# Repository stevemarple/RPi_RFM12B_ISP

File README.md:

# RPi_RFM12B_ISP

RFM12B and Atmel ISP programmer shield for Raspberry Pi

## Avrdude

Use the patched version of avrdude from http://project-downloads.drogon.net/files/. I suggest copying the
.avrduderc file from the avrdude directory in this repository to your home directory. It will create create 
the correct definitions for two new programmers, gpio0 for the onboard microcontroller and gpio1 for programming
other microcontrollers.

## Using the Arduino IDE

If you do not have a <code>hardware</code> directory inside your Arduino <code>sketchbook</code> folder
then create one. Copy the raspi directory and its entire contents to the hardware directory. Restart the 
Arduino IDE. You should now have two new board options, <code>ATmega328 @ 8MHz on RasPi</code> and 
<code>ATmega328P @ 8MHz on RasPi</code>. Select the one which matches the microcontroller. There are also two new
programmers; <code>Raspberry Pi GPIO (onboard)</code> and <code>Raspberry Pi GPIO (external ISP)</code>. 
The onboard one will be used automatically to upload new sketches to the RFM12B/ISP shield. The external ISP
programmer can be selected to program other microcontrollers from within the Arduino IDE.

## License

Unless indicated otherwise hardware is released under the Creative
Commons Attribution-ShareAlike 3.0 Unported (CC BY-SA 3.0)
http://creativecommons.org/licenses/by-sa/3.0/

Unless indicated otherwise software is released under the GNU Lesser
General Public License, version 2.1.
http://www.gnu.org/licenses/lgpl-2.1.html

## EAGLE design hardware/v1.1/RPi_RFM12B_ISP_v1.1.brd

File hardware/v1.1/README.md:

# RPi_RFM12B_ISP v1.1

Adds the reset line which was missing for the external programmer on
v1.

**Not tested**

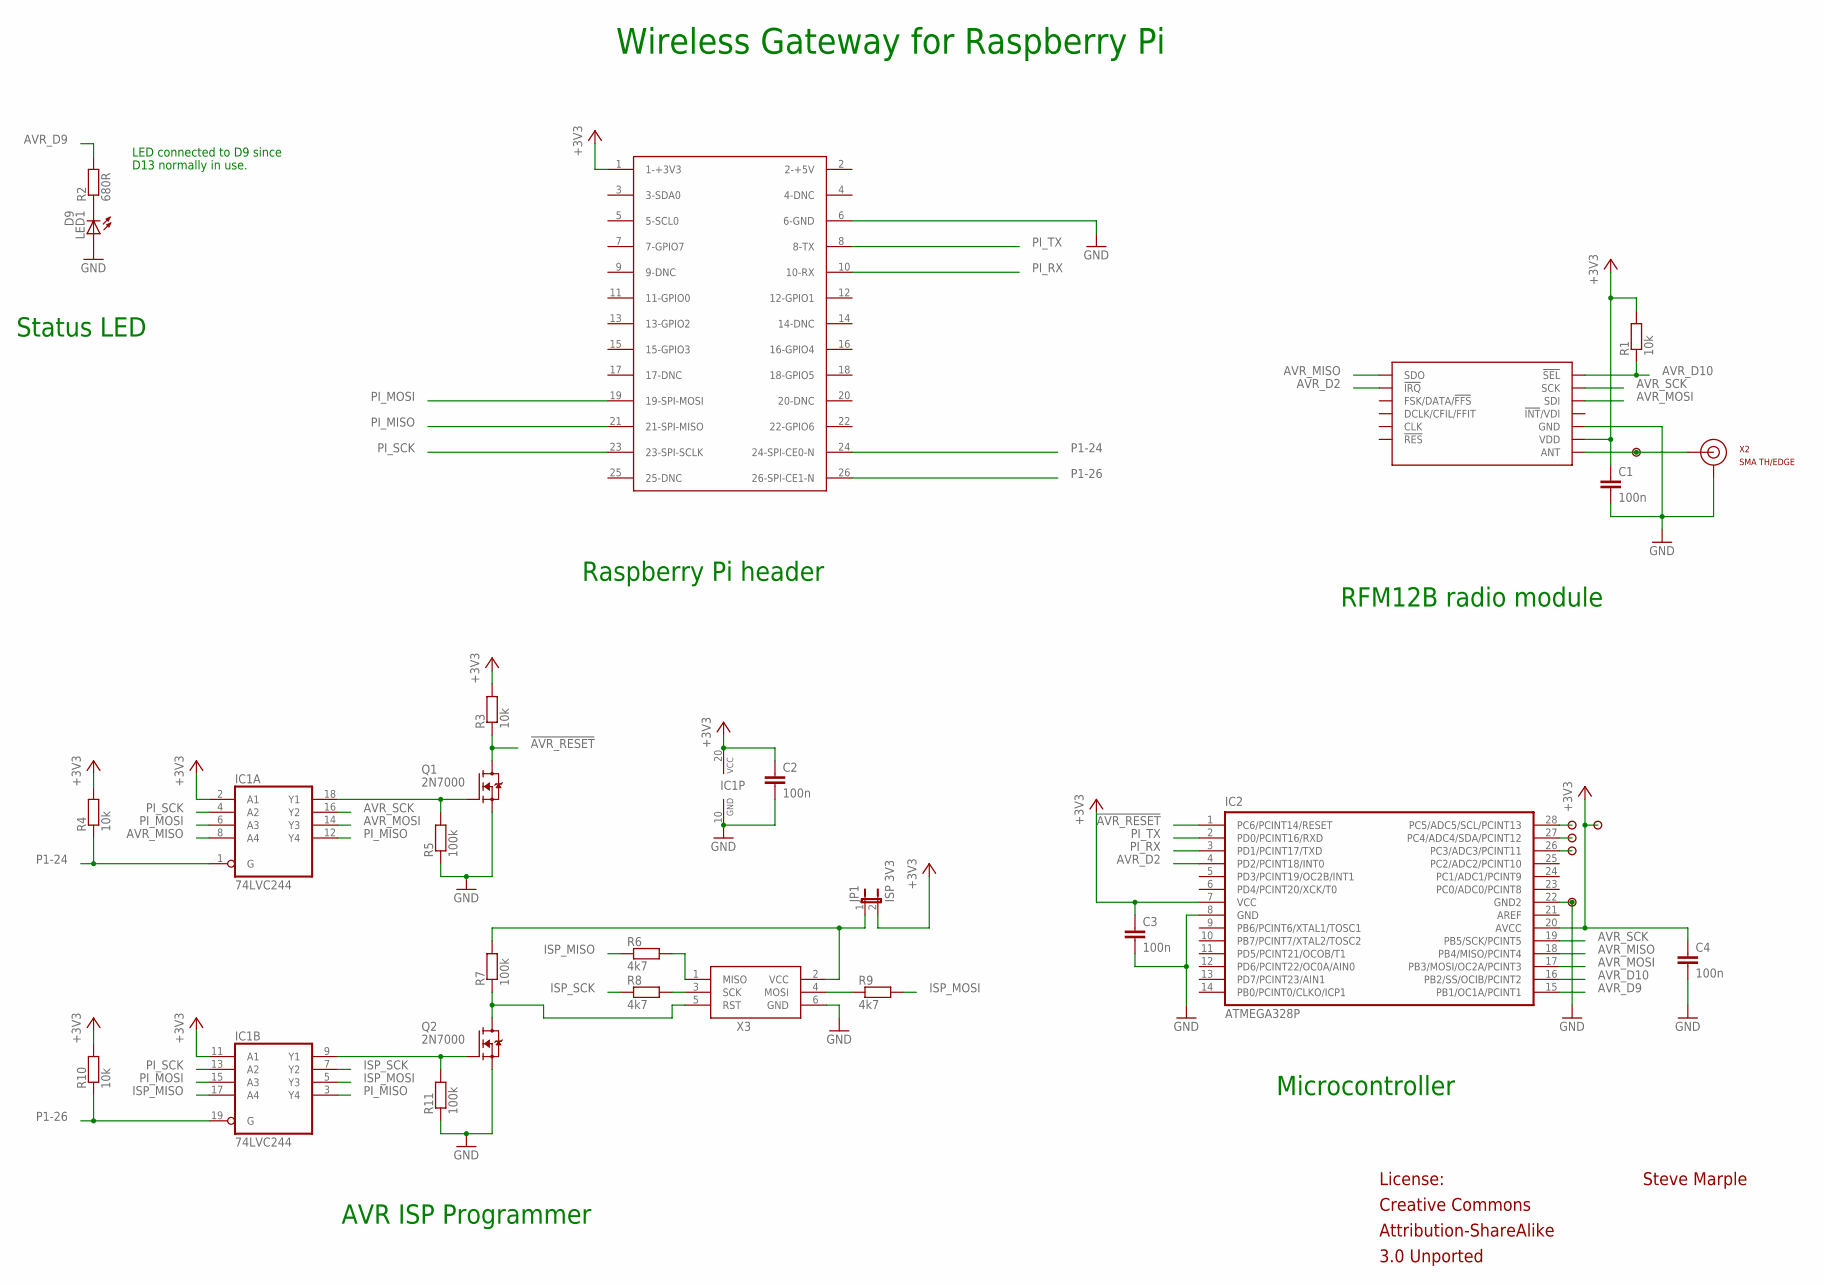
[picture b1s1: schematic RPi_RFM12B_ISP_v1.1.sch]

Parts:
AVR_A1, AVR_A2, AVR_A3, AVR_A4, AVR_A5: PAD
C1, C2, C3, C4: 100n; CAP-PTH-SMALL
IC1: 74LVC244; DIL20
IC2: ATMEGA328P; DIL28-N
JP1: ISP 3V3; 1X02
LED1: D9; LED3MM
Q1, Q2: 2N7000; TO-92
R1, R3, R4, R10: 10k; RES-AXIAL-0.4
R2: 680R; RES-AXIAL-0.4
R5, R7, R11: 100k; RES-AXIAL-0.4
R6, R8, R9: 4k7; RES-AXIAL-0.4
RF1: RFM12B
RFM12B_ANT: PAD
X1: P1A; RASPBERRY-PI-HEADER
X2: SMA TH/EDGE; SMA-THD-EDGE
X3: AVR ISP; CONN-HARTING-ML6

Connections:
!AVR_RESET: IC2.1 (PC6/PCINT14/RESET), Q1.3 (D), R3.P$1 (1)
+3V3: AVR_A5.1, C1.1, C2.1, C3.1, C4.1, IC1.2 (A1), IC1.11 (A1), IC1.20 (VCC), IC2.7 (VCC), IC2.20 (AVCC), JP1.2, R1.P$2 (2), R3.P$2 (2), R4.P$2 (2), R10.P$2 (2), RF1.VDD, X1.1 (1-+3V3)
AVR_D2: IC2.4 (PD2/PCINT18/INT0), RF1.!IRQ
AVR_D9: IC2.15 (PB1/OC1A/PCINT1), R2.P$2 (2)
AVR_D10: IC2.16 (PB2/SS/OCIB/PCINT2), R1.P$1 (1), RF1.!SEL
AVR_MISO: IC1.8 (A4), IC2.18 (PB4/MISO/PCINT4), RF1.SDO
AVR_MOSI: IC1.14 (Y3), IC2.17 (PB3/MOSI/OC2A/PCINT3), RF1.SDI
AVR_SCK: IC1.16 (Y2), IC2.19 (PB5/SCK/PCINT5), RF1.SCK
GND: AVR_A4.1, C1.2, C2.2, C3.2, C4.2, IC1.10 (GND), IC2.8 (GND), IC2.22 (GND2), LED1.A, Q1.1 (S), Q2.1 (S), R5.P$1 (1), R11.P$1 (1), RF1.GND@0 (GND), RF1.GND@1 (GND), X1.6 (6-GND), X2.GND@0 (GND), X2.GND@1 (GND), X2.GND@2 (GND), X2.GND@3 (GND), X2.GND@EDGE0 (GND), X2.GND@EDGE1 (GND), X2.GND@EDGE2 (GND), X2.GND@EDGE3 (GND), X3.6 (GND)
ISP_MISO: IC1.17 (A4), R6.P$1 (1)
ISP_MOSI: IC1.5 (Y3), R9.P$2 (2)
ISP_SCK: IC1.7 (Y2), R8.P$1 (1)
unnamed: RF1.ANT, RFM12B_ANT.1, X2.SIG (SIGNAL), X2.SIG@EDGE (SIGNAL)
unnamed: LED1.K (C), R2.P$1 (1)
unnamed: AVR_A1.1, IC2.28 (PC5/ADC5/SCL/PCINT13)
unnamed: AVR_A2.1, IC2.27 (PC4/ADC4/SDA/PCINT12)
unnamed: AVR_A3.1, IC2.26 (PC3/ADC3/PCINT11)
unnamed: IC1.18 (Y1), Q1.2 (G), R5.P$2 (2)
unnamed: R8.P$2 (2), X3.3 (SCK)
unnamed: R6.P$2 (2), X3.1 (MISO)
unnamed: IC1.9 (Y1), Q2.2 (G), R11.P$2 (2)
unnamed: Q2.3 (D), R7.P$1 (1), X3.5 (RST)
unnamed: JP1.1, R7.P$2 (2), X3.2 (VCC)
unnamed: R9.P$1 (1), X3.4 (MOSI)
P1-24: IC1.1 (G), R4.P$1 (1), X1.24 (24-SPI-CE0-N)
P1-26: IC1.19 (G), R10.P$1 (1), X1.26 (26-SPI-CE1-N)
PI_MISO: IC1.3 (Y4), IC1.12 (Y4), X1.21 (21-SPI-MISO)
PI_MOSI: IC1.6 (A3), IC1.15 (A3), X1.19 (19-SPI-MOSI)
PI_RX: IC2.3 (PD1/PCINT17/TXD), X1.10 (10-RX)
PI_SCK: IC1.4 (A2), IC1.13 (A2), X1.23 (23-SPI-SCLK)
PI_TX: IC2.2 (PD0/PCINT16/RXD), X1.8 (8-TX)

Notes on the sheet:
Raspberry Pi header
RFM12B radio module
Wireless Gateway for Raspberry Pi
AVR ISP Programmer
Steve Marple
Creative Commons
Attribution-ShareAlike
3.0 Unported
License:
Status LED
LED connected to D9 since
D13 normally in use.
Microcontroller

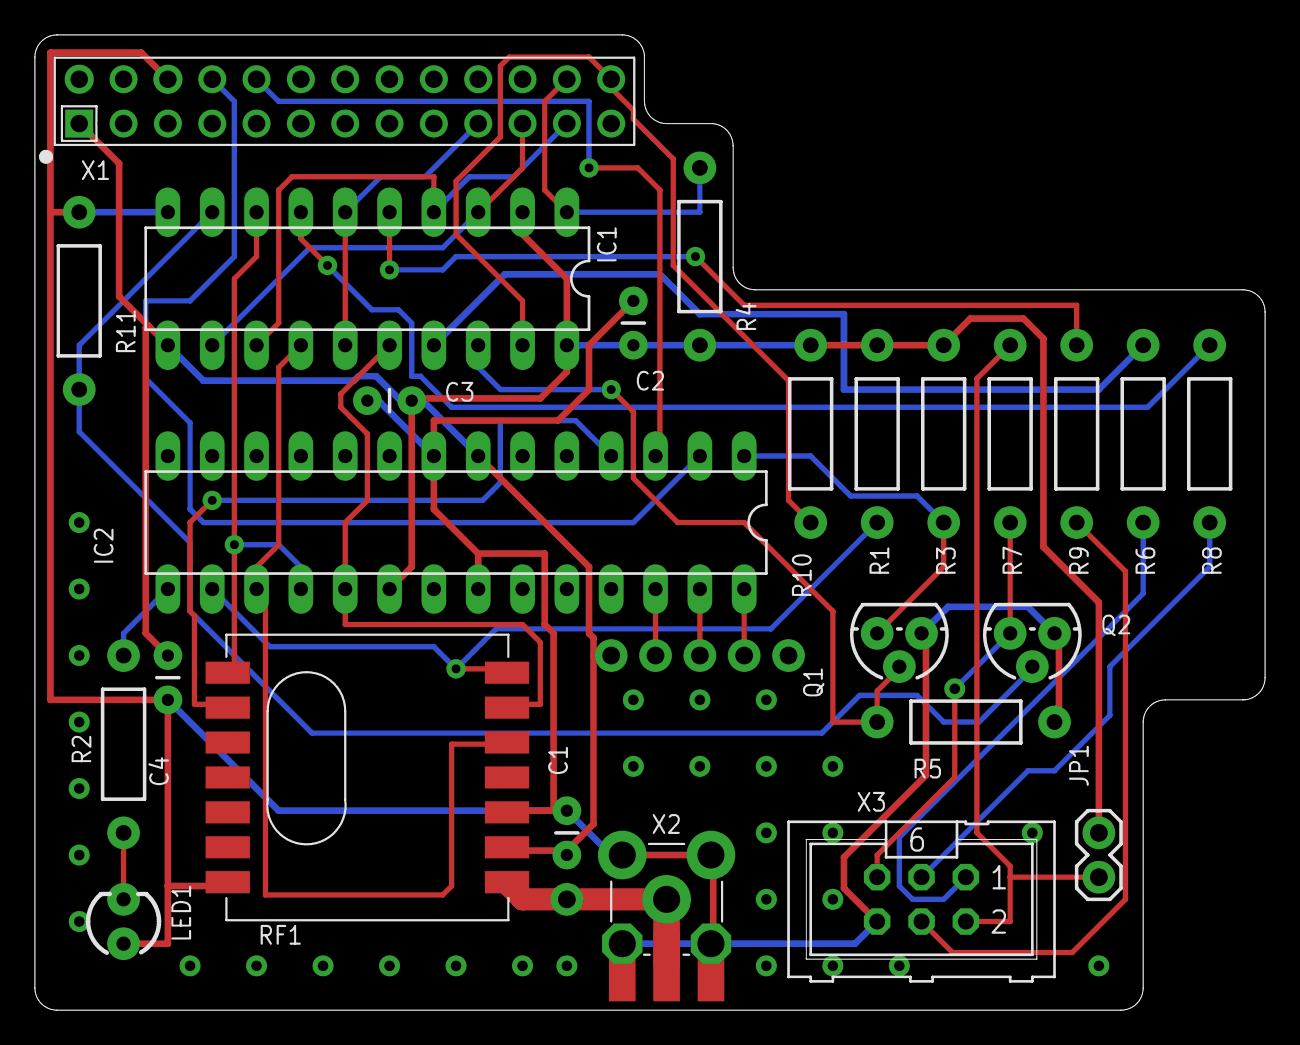
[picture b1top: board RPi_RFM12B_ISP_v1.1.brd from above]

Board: 2 copper layers, 70.5 x 55.9 mm, 31 parts (0 on the bottom side), 31 nets.

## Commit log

2012-12-28 Adding schematic and board files for preliminary version.
2013-02-08 Creating separate directory for hardware design files.
2013-02-08 Adding Arduino IDE and avrdude files.
2013-02-08 Adding/updating to final Eagle PCB files.
2013-02-08 Adding Gerber files.
2013-02-11 Updated license information.
2013-02-11 Setting brown-out detection (2.7V) in the fuses.
2013-02-15 Preliminary design for version 1.1.
    Adding missing /RESET connection for external ISP header. Removing cutout since board is too high for the Multicomp case. Adding +3.3V and ground pads.
2013-03-11 Adding local copies of the debian install files for the patched avrdude.
2013-05-23 Adding gpio0 and gpio1 definitions to .avrduderc
2013-06-30 Adding design rules and CAM files used for creation of Gerber files.
2013-06-30 Adding README file to describe current production status.

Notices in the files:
hardware/v1.1/RPi_RFM12B_ISP_v1.1.brd:
License: CC BY-SA 3.0
parts and their libraries:
SparkFun: Licensing: CC v3.0 Share-Alike You are welcome to use this library for commercial purposes.
